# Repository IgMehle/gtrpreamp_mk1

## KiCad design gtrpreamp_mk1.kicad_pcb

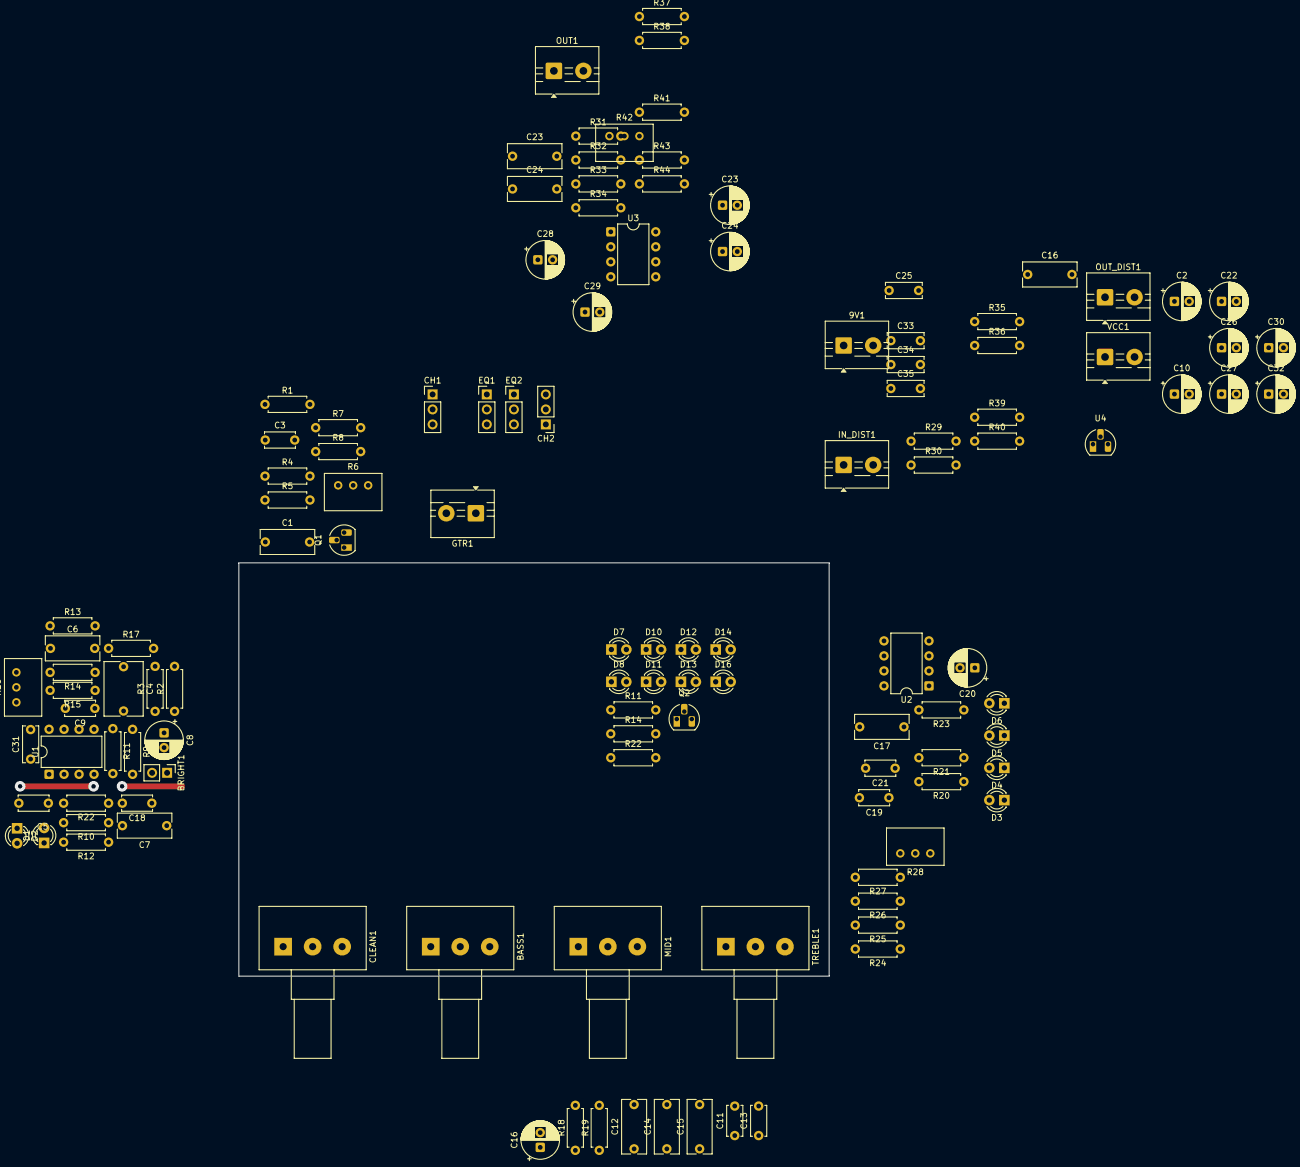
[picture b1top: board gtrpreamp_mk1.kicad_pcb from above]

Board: 2 copper layers, 100.0 x 70.0 mm, 120 parts (0 on the bottom side), 67 nets.

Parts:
9V1: BORNE; TerminalBlock_MaiXu_MX126-5.0-02P_1x02_P5.00mm
BASS1: 1M; Potentiometer_Alps_RK163_Single_Horizontal
BRIGHT1: SW_SPST; PinHeader_1x02_P2.54mm_Vertical
C1, C14: 47n; C_Rect_L9.0mm_W4.0mm_P7.50mm_MKT
C2, C10, C26, C27, C29, C30, C32: 10u; CP_Radial_D6.3mm_P2.50mm
C3: 100p; C_Disc_D5.0mm_W2.5mm_P5.00mm
C4: 220n; C_Rect_L9.0mm_W6.4mm_P7.50mm_MKT
C5, C9, C11: 150p; C_Disc_D5.0mm_W2.5mm_P5.00mm
C6, C15: 100n; C_Rect_L9.0mm_W4.0mm_P7.50mm_MKT
C7, C17: 220n; C_Rect_L9.0mm_W4.0mm_P7.50mm_MKT
C8, C16, C20, C22, C23#2, C24, C28: 1u; CP_Radial_D6.3mm_P2.50mm
C12: 22n; C_Rect_L9.0mm_W4.0mm_P7.50mm_MKT
C13, C19, C21: 220p; C_Disc_D5.0mm_W2.5mm_P5.00mm
C16#2, C23, C24#2: 470n; C_Rect_L9.0mm_W4.0mm_P7.50mm_MKT
C18: 4n7; C_Disc_D5.0mm_W2.5mm_P5.00mm
C25, C31, C33, C34, C35: 0.1u; C_Disc_D6.0mm_W2.5mm_P5.00mm
CH1, CH2: SW_SPDT; PinHeader_1x03_P2.54mm_Vertical
CLEAN1: 100k; Potentiometer_Alps_RK163_Single_Horizontal
D1, D2, D3, D4, D5, D6, D7, D8, D10, D11, D12, D13, D14, D16: LED; LED_D3.0mm_Clear
EQ1, EQ2: SW_SPDT; PinHeader_1x03_P2.54mm_Vertical
GTR1: BORNE; TerminalBlock_MaiXu_MX126-5.0-02P_1x02_P5.00mm
IN_DIST1: BORNE; TerminalBlock_MaiXu_MX126-5.0-02P_1x02_P5.00mm
MID1: 25k; Potentiometer_Alps_RK163_Single_Horizontal
OUT1: BORNE; TerminalBlock_MaiXu_MX126-5.0-02P_1x02_P5.00mm
OUT_DIST1: BORNE; TerminalBlock_MaiXu_MX126-5.0-02P_1x02_P5.00mm
Q1, Q2: 2N5457; TO-92_HandSolder
R1, R5: 2M2; R_Axial_DIN0207_L6.3mm_D2.5mm_P7.62mm_Horizontal
R2, R3, R11#2, R21, R35, R36, R39, R40: 22k; R_Axial_DIN0207_L6.3mm_D2.5mm_P7.62mm_Horizontal
R4, R10, R18: 33k; R_Axial_DIN0207_L6.3mm_D2.5mm_P7.62mm_Horizontal
R6: 5k; Potentiometer_Bourns_3299W_Vertical
R7, R11, R17, R23, R30, R37, R38, R43: 1k; R_Axial_DIN0207_L6.3mm_D2.5mm_P7.62mm_Horizontal
R8: 680; R_Axial_DIN0207_L6.3mm_D2.5mm_P7.62mm_Horizontal
R9, R19, R20, R24, R33, R34: 100k; R_Axial_DIN0207_L6.3mm_D2.5mm_P7.62mm_Horizontal
R12, R14, R15, R26: 6k8; R_Axial_DIN0207_L6.3mm_D2.5mm_P7.62mm_Horizontal
R13, R29, R31, R32, R41: 1M; R_Axial_DIN0207_L6.3mm_D2.5mm_P7.62mm_Horizontal
R14#2, R25: 10k; R_Axial_DIN0207_L6.3mm_D2.5mm_P7.62mm_Horizontal
R16: 50k; Potentiometer_Bourns_3299W_Vertical
R22: 4K7; R_Axial_DIN0207_L6.3mm_D2.5mm_P7.62mm_Horizontal
R22#2: 4k7; R_Axial_DIN0207_L6.3mm_D2.5mm_P7.62mm_Horizontal
R27: 15k; R_Axial_DIN0207_L6.3mm_D2.5mm_P7.62mm_Horizontal
R28, R42: 10k; Potentiometer_Bourns_3299W_Vertical
R44: 100; R_Axial_DIN0207_L6.3mm_D2.5mm_P7.62mm_Horizontal
TREBLE1: 250k; Potentiometer_Alps_RK163_Single_Horizontal
U1, U2, U3: NE5532; DIP-8_W7.62mm
U4: L78L09_TO92; TO-92_HandSolder
VCC1: BORNE; TerminalBlock_MaiXu_MX126-5.0-02P_1x02_P5.00mm

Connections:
9V: 9V1.1, C30.1, C35.2, U4.1 (VO)
BIAS1: BRIGHT1.1 (A), C2.1, C7.1, C8.2, R2.1, R3.2, R9.2
BIAS2: C17.1, C20.2, C27.1, R20.2, R35.1, R36.2
BIAS3: C32.1, R33.2, R34.2, R39.1, R40.2
CH2: C23.1, C24.2, OUT_DIST1.1, R31.2
CHANNELS: CH2.2 (B), EQ1.3 (C), R18.2
CLEAN: CH2.1 (A), R17.2
DIST: CH2.3 (C), R43.2
EQ1: C11.2, C13.1, EQ1.1 (A)
EQ2: C11.1, EQ1.2 (B), R18.1, R19.1
EQ4: C12.2, C15.1, EQ2.1 (A)
EQ5: C12.1, C14.1, EQ2.2 (B), R19.2
FX_RETURN: C23#2.2, C24#2.1, R32.2
GND: 9V1.2, C2.2, C3.1, C10.2, C25.1, C26.2, C27.2, C30.2, C31.1, C32.2, C33.1, C34.1, C35.1, GTR1.2, IN_DIST1.2, MID1.1, OUT1.2, OUT_DIST1.2, R1.1, R3.1, R5.1, R7.1, R8.1, R13.1, R14#2.1, R29.1, R31.1, R32.1, R36.1, R40.1, R41.1, R42.1, U1.4 (V-), U2.4 (V-), U3.4 (V-), U4.2 (GND), VCC1.2
GTR: CH1.2 (B), GTR1.1
IN1: C1.1, CH1.1 (A), R1.2
IN2: CH1.3 (C), IN_DIST1.1
unnamed: BASS1.1, C15.2, MID1.2, MID1.3
unnamed: BASS1.2, BASS1.3, C14.2, TREBLE1.1
unnamed: BRIGHT1.2 (B), C18.1
unnamed: C1.2, R4.1
unnamed: C4.2, R10.1, R11.1
unnamed: C6.2, R13.2, R17.1
unnamed: C8.1, R11#2.1, R14.1
unnamed: C13.2, TREBLE1.3
unnamed: C16.1, C16#2.1, R20.1, R23.1
unnamed: C16.2, C16#2.2, TREBLE1.2
unnamed: C17.2, R21.1
unnamed: C18.2, R22.1, R22#2.1
unnamed: C20.1, R26.1
unnamed: C22.2, R29.2, R30.1
unnamed: C23#2.1, R34.1, R38.1
unnamed: C24.1, R33.1, R37.1
unnamed: C28.2, R41.2, R43.1
unnamed: C29.2, R42.3
unnamed: CLEAN1.1, D1.2 (A), D2.1 (K)
unnamed: C9.1, D1.1 (K), D7.2 (A), R11#2.2, R12.2, R22#2.2, U1.6 (-)
unnamed: D3.2 (A), D5.1 (K)
unnamed: C19.1, D3.1 (K), D4.2 (A), R21.2, R24.1, U2.2 (-)
unnamed: D4.1 (K), D6.2 (A)
unnamed: D5.2 (A), D6.1 (K), R24.2, R25.1
unnamed: D7.1 (K), D8.2 (A)
unnamed: D8.1 (K), D10.2 (A)
unnamed: C6.1, C9.2, D10.1 (K), R16.2, R16.3, U1.7
unnamed: D11.2 (A), D13.1 (K)
unnamed: C21.1, D11.1 (K), D12.2 (A), R26.2, R27.1, U2.6 (-)
unnamed: D12.1 (K), D14.2 (A)
unnamed: D14.1 (K), D16.2 (A)
unnamed: C21.2, C22.1, D16.1 (K), R28.2, R28.3, U2.7
unnamed: Q1.1 (D), Q2.3 (G), R6.3
unnamed: C3.2, Q1.3 (G), R4.2, R5.2
unnamed: Q1.2 (S), R7.2, R8.2
unnamed: C4.1, Q2.2 (S), R14#2.2
unnamed: R27.2, R28.1
unnamed: R42.2, R44.1
unnamed: R9.1, R11.2, U1.3 (+)
unnamed: C5.1, CLEAN1.2, CLEAN1.3, R10.2, R12.1, R22.2, U1.2 (-)
unnamed: C5.2, U1.1, U1.5 (+)
unnamed: R14.2, R15.1
unnamed: R23.2, U2.3 (+)
unnamed: C19.2, R25.2, U2.1, U2.5 (+)
unnamed: R37.2, U3.3 (+)
unnamed: C28.1, U3.1, U3.2 (-)
unnamed: R38.2, U3.5 (+)
unnamed: C29.1, U3.6 (-), U3.7
OUT: OUT1.1, R44.2
VCC: C10.1, C25.2, C26.1, C31.2, C33.2, C34.2, Q2.1 (D), R2.2, R6.1, R6.2, R35.2, R39.2, U1.8 (V+), U2.8 (V+), U3.8 (V+), U4.3 (VI), VCC1.1
